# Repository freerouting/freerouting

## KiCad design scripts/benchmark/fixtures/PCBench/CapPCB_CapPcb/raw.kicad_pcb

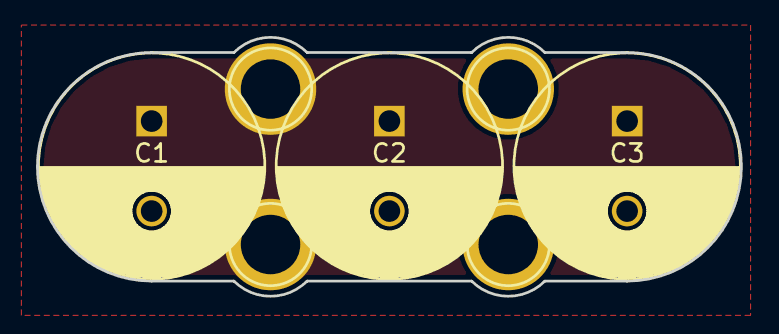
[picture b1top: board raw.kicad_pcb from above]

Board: 2 copper layers, 39.1 x 14.4 mm, 7 parts (0 on the bottom side), 2 nets, no tracks yet.

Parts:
C1, C2, C3: 560uF, 63V; C_Radial_D12.5_L25_P5
P1, P3: +; 1pin
P2, P4: -; 1pin

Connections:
unnamed: C1.1, C2.1, C3.1, P1.1, P3.1
unnamed: C1.2, C2.2, C3.2, P2.1, P4.1

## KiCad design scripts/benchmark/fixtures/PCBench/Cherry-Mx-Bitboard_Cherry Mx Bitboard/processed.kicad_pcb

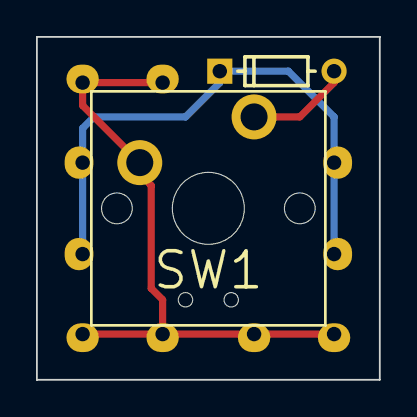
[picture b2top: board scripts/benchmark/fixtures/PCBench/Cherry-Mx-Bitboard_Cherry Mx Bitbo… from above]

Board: 2 copper layers, 19.0 x 19.0 mm, 12 parts (1 on the bottom side), 3 nets.

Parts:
D1: D; diode
P11, P12, P13, P14, P15, P16, P21, P22, P23, P24: CONN_01X01; wirepad
SW1: SW_PUSH; switch

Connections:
/1: P11.1, P12.1, P13.1, P14.1, P15.1, P16.1, SW1.1
/2: D1.1, P21.1, P22.1, P23.1, P24.1
unnamed: D1.2, SW1.2

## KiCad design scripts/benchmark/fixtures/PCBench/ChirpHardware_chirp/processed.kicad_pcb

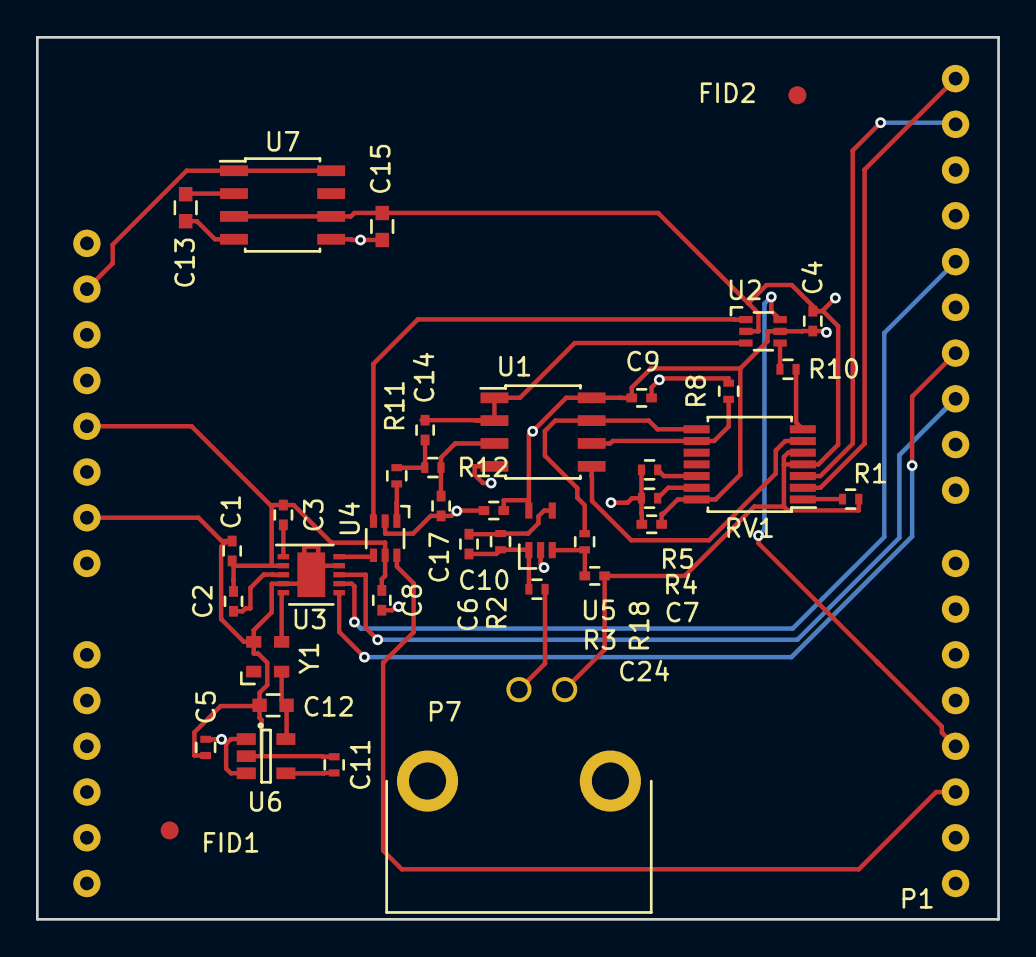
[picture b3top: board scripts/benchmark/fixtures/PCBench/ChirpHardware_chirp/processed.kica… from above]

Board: 4 copper layers, 53.4 x 49.0 mm, 40 parts (0 on the bottom side), 35 nets.

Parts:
C1, C2, C3, C6, C14, C17, C24: C; C_0402
C4, C8, C9, C10: 0.01uF; C_0402
C5: 1uF; R_0402
C7: 0.1uF; C_0402
C11: 10nF; R_0402
C12: 2.2uF; C_0603
C13, C15: C; C_0603
FID1, FID2: Fiducial_1mm_Dia_2.54mm_Outer_CopperTop
P1: Arduino
P7: BNC; TE_BNC
R1, R4, R5: 0; R_0402
R2, R3, R11, R12, R18: R; R_0402
R8, R10: 2k; R_0402
RV1: MCP4651; TSSOP-14_4.4x5mm_Pitch0.65mm
U1: opa2335; SOIC-8_3.9x4.9mm_Pitch1.27mm
U2, U4: MUX; SC-70-6
U3: AD9837; DFN-10-1EP_3x3mm_Pitch0.5mm
U5: LMH6657; SOT23-5
U6: LP2985LV; SOT-23-5
U7: LM2660; SOIC-8_3.9x4.9mm_Pitch1.27mm
Y1: ASDMB-16MHZ; ADSM-16

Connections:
+5V: C1.1, C2.2, C3.1, C4.1, C5.1, C7.1, C8.1, C9.1, C10.1, P1.10, P1.13, P1.30, RV1.14, U1.8, U2.5, U3.2, U4.5, U5.5, U6.1, U6.3, U7.1, U7.8
Filter_IN: R11.2, U4.1
Filtered: C14.2, U1.1, U1.2, U2.3
GND: C1.2, C4.2, C5.2, C7.2, C8.2, C9.2, C10.2, C11.2, C12.2, C15.2, C17.2, C24.2, P1.8, P1.9, P1.29, P7.2, R1.2, R4.1, R5.1, R8.2, RV1.4, RV1.5, U2.2, U3.4, U3.9, U3.11, U4.2, U6.2, U7.3, U7.6, Y1.2
MOSI: P1.26, U3.6
unnamed: C2.1, U3.3
unnamed: C3.2, U3.1
unnamed: C6.1, R2.1, R3.2, U5.1
unnamed: C6.2, R2.2, U5.4
unnamed: C11.1, U6.4
unnamed: C12.1, U6.5, Y1.4
unnamed: C13.1, U7.2
unnamed: C13.2, U7.4
unnamed: C14.1, R11.1, R12.2
unnamed: C17.1, R12.1, U1.3
unnamed: C24.1, R18.1, U5.3
unnamed: P7.1, R3.1
unnamed: R1.1, RV1.1
unnamed: R4.2, RV1.13
unnamed: R5.2, RV1.12
unnamed: R8.1, RV1.9, U1.6
unnamed: R10.1, RV1.7
unnamed: R10.2, U2.4
unnamed: R18.2, RV1.8, U1.7
unnamed: RV1.6, U1.5
unnamed: U3.5, Y1.3
OUT: U3.10, U4.4
SCL: P1.32, RV1.2
SCLK: P1.28, U3.7
SDA: P1.31, RV1.3
SELECT_0: P1.17, U4.6
SELECT_1: P1.18, U2.6
SS: P1.25, U3.8
Square: U2.1, U4.3
VEE: C15.1, U1.4, U5.2, U7.5
